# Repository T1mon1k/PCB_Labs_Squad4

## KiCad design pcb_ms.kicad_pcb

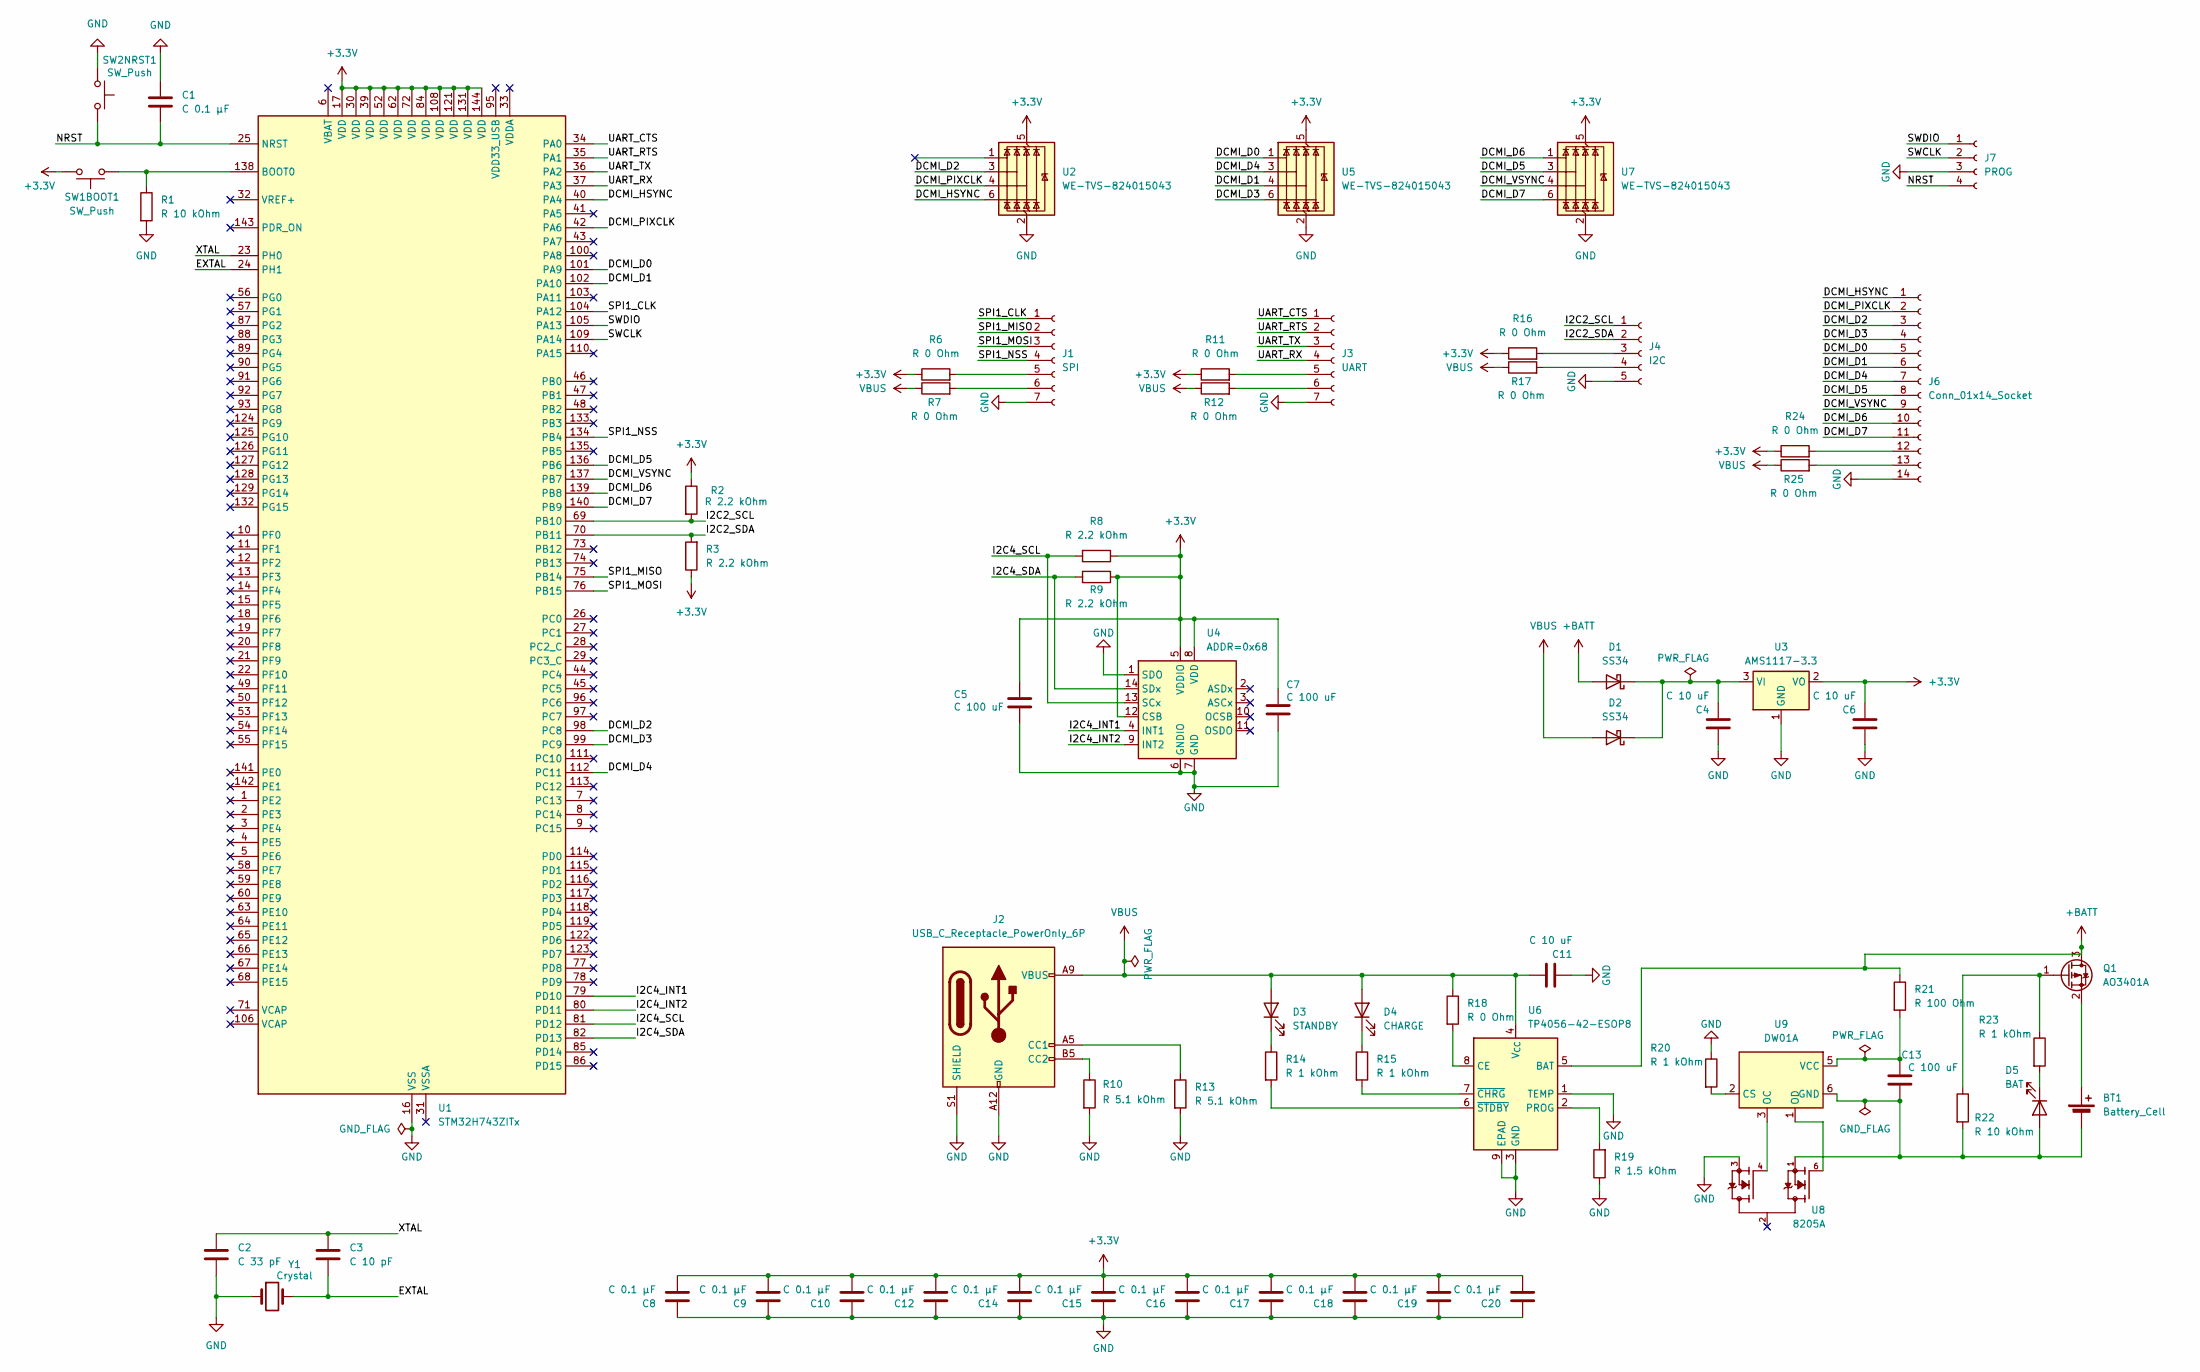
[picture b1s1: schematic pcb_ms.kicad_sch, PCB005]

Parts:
BT1: Battery_Cell; BatteryHolder_Keystone_1042_1x18650
C1, C8, C9, C10, C12, C14, C15, C16, C17, C18, C19, C20: C 0.1 μF; C_0805_2012Metric_Pad1.18x1.45mm_HandSolder
C2: C 33 pF; C_0805_2012Metric_Pad1.18x1.45mm_HandSolder
C3: C 10 pF; C_0805_2012Metric_Pad1.18x1.45mm_HandSolder
C4, C6, C11: C 10 uF; C_0805_2012Metric_Pad1.18x1.45mm_HandSolder
C5, C7, C13: C 100 uF; C_0805_2012Metric_Pad1.18x1.45mm_HandSolder
D1, D2: SS34; D_SMA
D3: STANDBY; LED_0805_2012Metric
D4: CHARGE; LED_0805_2012Metric
D5: BAT; LED_0805_2012Metric
J1: SPI; JST_ZH_S7B-ZR-SM4A-TF_1x07-1MP_P1.50mm_Horizontal
J2: USB_C_Receptacle_PowerOnly_6P; USB_C_Receptacle_GCT_USB4125-xx-x-0190_6P_TopMnt_Horizontal
J3: UART; JST_ZH_S7B-ZR-SM4A-TF_1x07-1MP_P1.50mm_Horizontal
J4: I2C; JST_ZH_S5B-ZR-SM4A-TF_1x05-1MP_P1.50mm_Horizontal
J6: Conn_01x14_Socket; JST_SH_SM14B-SRSS-TB_1x14-1MP_P1.00mm_Horizontal
J7: PROG; JST_ZH_S4B-ZR-SM4A-TF_1x04-1MP_P1.50mm_Horizontal
Q1: AO3401A; SOT-23
R1, R22: R 10 kOhm; R_0805_2012Metric_Pad1.20x1.40mm_HandSolder
R2, R3, R8, R9: R 2.2 kOhm; R_0805_2012Metric_Pad1.20x1.40mm_HandSolder
R6, R7, R11, R12, R16, R17, R18, R24, R25: R 0 Ohm; R_0805_2012Metric_Pad1.20x1.40mm_HandSolder
R10, R13: R 5.1 kOhm; R_0805_2012Metric_Pad1.20x1.40mm_HandSolder
R14, R15, R20, R23: R 1 kOhm; R_0805_2012Metric_Pad1.20x1.40mm_HandSolder
R19: R 1.5 kOhm; R_0805_2012Metric_Pad1.20x1.40mm_HandSolder
R21: R 100 Ohm; R_0805_2012Metric_Pad1.20x1.40mm_HandSolder
SW1BOOT1, SW2NRST1: SW_Push; SW_PUSH_6mm
U1: STM32H743ZITx; LQFP-144_20x20mm_P0.5mm
U2, U5, U7: WE-TVS-824015043; SOT-23-6
U3: AMS1117-3.3; SOT-223-3_TabPin2
U4: ADDR=0x68; Bosch_LGA-14_3x2.5mm_P0.5mm
U6: TP4056-42-ESOP8; SOIC-8-1EP_3.9x4.9mm_P1.27mm_EP2.41x3.3mm_ThermalVias
U8: 8205A; SOT95P285X140-6N; PARTREV NA
U9: DW01A; SOT-23-6
Y1: Crystal; Crystal_SMD_5032-2Pin_5.0x3.2mm_HandSoldering

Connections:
+3.3V: C5.2, C6.2, C7.2, C8.2, C9.2, C10.2, C12.2, C14.2, C15.2, C16.2, C17.2, C18.2, C19.2, C20.2, R2.1, R3.1, R6.1, R8.1, R9.1, R11.1, R16.1, R24.1, SW1BOOT1.2, U1.17 (VDD), U1.30 (VDD), U1.39 (VDD), U1.52 (VDD), U1.62 (VDD), U1.72 (VDD), U1.84 (VDD), U1.108 (VDD), U1.121 (VDD), U1.131 (VDD), U1.144 (VDD), U2.5 (VBUS), U3.2 (VO), U4.5 (VDDIO), U4.8 (VDD), U4.12 (CSB), U5.5 (VBUS), U7.5 (VBUS)
+BATT: D1.2 (A), Q1.3 (D), R21.1, U6.5 (BAT)
/DCMI_D0: J6.5, U1.101 (PA9), U5.1 (I/O1)
/DCMI_D1: J6.6, U1.102 (PA10), U5.4 (I/O3)
/DCMI_D2: J6.3, U1.98 (PC8), U2.3 (I/O2)
/DCMI_D3: J6.4, U1.99 (PC9), U5.6 (I/O4)
/DCMI_D4: J6.7, U1.112 (PC11), U5.3 (I/O2)
/DCMI_D5: J6.8, U1.136 (PB6), U7.3 (I/O2)
/DCMI_D6: J6.10, U1.139 (PB8), U7.1 (I/O1)
/DCMI_D7: J6.11, U1.140 (PB9), U7.6 (I/O4)
/DCMI_HSYNC: J6.1, U1.40 (PA4), U2.6 (I/O4)
/DCMI_PIXCLK: J6.2, U1.42 (PA6), U2.4 (I/O3)
/DCMI_VSYNC: J6.9, U1.137 (PB7), U7.4 (I/O3)
/EXTAL: C3.2, U1.24 (PH1), Y1.2
/I2C2_SCL: J4.1, R2.2, U1.69 (PB10)
/I2C2_SDA: J4.2, R3.2, U1.70 (PB11)
/I2C4_INT1: U1.79 (PD10), U4.4 (INT1)
/I2C4_INT2: U1.80 (PD11), U4.9 (INT2)
/I2C4_SCL: R8.2, U1.81 (PD12), U4.13 (SCx)
/I2C4_SDA: R9.2, U1.82 (PD13), U4.14 (SDx)
/NRST: C1.2, J7.4, SW2NRST1.2, U1.25 (NRST)
/SPI1_CLK: J1.1, U1.104 (PA12)
/SPI1_MISO: J1.2, U1.75 (PB14)
/SPI1_MOSI: J1.3, U1.76 (PB15)
/SPI1_NSS: J1.4, U1.134 (PB4)
/SWCLK: J7.2, U1.109 (PA14)
/SWDIO: J7.1, U1.105 (PA13)
/UART_CTS: J3.1, U1.34 (PA0)
/UART_RTS: J3.2, U1.35 (PA1)
/UART_RX: J3.4, U1.37 (PA3)
/UART_TX: J3.3, U1.36 (PA2)
/XTAL: C2.1, C3.1, U1.23 (PH0)
GND: C1.1, C2.2, C4.1, C5.1, C6.1, C7.1, C8.1, C9.1, C10.1, C11.2, C12.1, C14.1, C15.1, C16.1, C17.1, C18.1, C19.1, C20.1, J1.7, J2.A12 (GND), J2.B12 (GND), J2.S1 (SHIELD), J3.7, J4.5, J6.14, J7.3, R1.2, R10.2, R13.2, R19.1, R20.1, SW2NRST1.1, U1.16 (VSS), U1.38 (VSS), U1.51 (VSS), U1.61 (VSS), U1.83 (VSS), U1.94 (VSS), U1.107 (VSS), U1.120 (VSS), U1.130 (VSS), U2.2 (GND), U3.1 (GND), U4.1 (SDO), U4.6 (GNDIO), U4.7 (GND), U5.2 (GND), U6.1 (TEMP), U6.3 (GND), U6.9 (EPAD), U7.2 (GND), U8.3, Y1.1
unnamed: BT1.1 (+), Q1.2 (S)
unnamed: BT1.2 (-), C13.1, D5.2 (A), R22.2, U8.1, U9.6 (GND)
unnamed: C4.2, D1.1 (K), D2.1 (K), U3.3 (VI)
unnamed: D3.1 (K), R14.1
unnamed: D4.1 (K), R15.1
unnamed: D5.1 (K), R23.2
unnamed: J1.5, R6.2
unnamed: J1.6, R7.2
unnamed: J2.A5 (CC1), R13.1
unnamed: J2.B5 (CC2), R10.1
unnamed: J3.5, R11.2
unnamed: J3.6, R12.2
unnamed: J4.3, R16.2
unnamed: J4.4, R17.2
unnamed: J6.12, R24.2
unnamed: J6.13, R25.2
unnamed: Q1.1 (G), R22.1, R23.1
unnamed: R1.1, SW1BOOT1.1, U1.138 (BOOT0)
unnamed: R18.2, U6.8 (CE)
unnamed: R19.2, U6.2 (PROG)
unnamed: R15.2, U6.7 (~CHRG)
unnamed: R14.2, U6.6 (~STDBY)
unnamed: R20.2, U9.2 (CS)
unnamed: U8.4, U9.3 (OC)
unnamed: U8.6, U9.1 (OD)
unnamed: C13.2, R21.2, U9.5 (VCC)
VBUS: C11.1, D2.2 (A), D3.2 (A), D4.2 (A), J2.A9 (VBUS), J2.B9 (VBUS), R7.1, R12.1, R17.1, R18.1, R25.1, U6.4 (V_{CC})

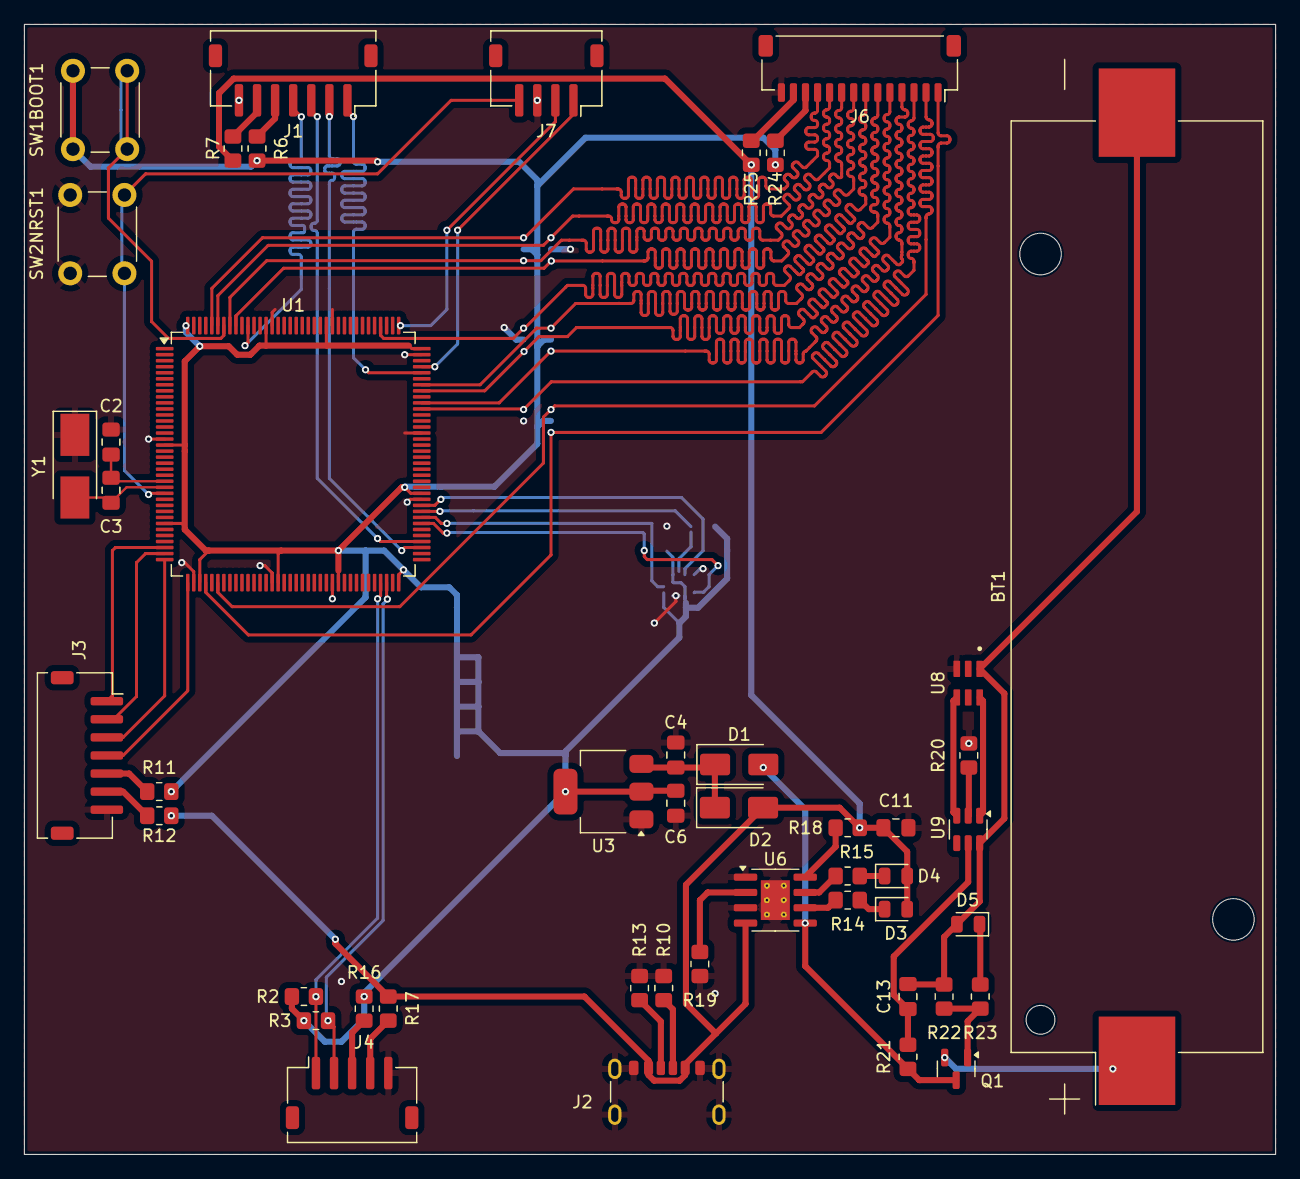
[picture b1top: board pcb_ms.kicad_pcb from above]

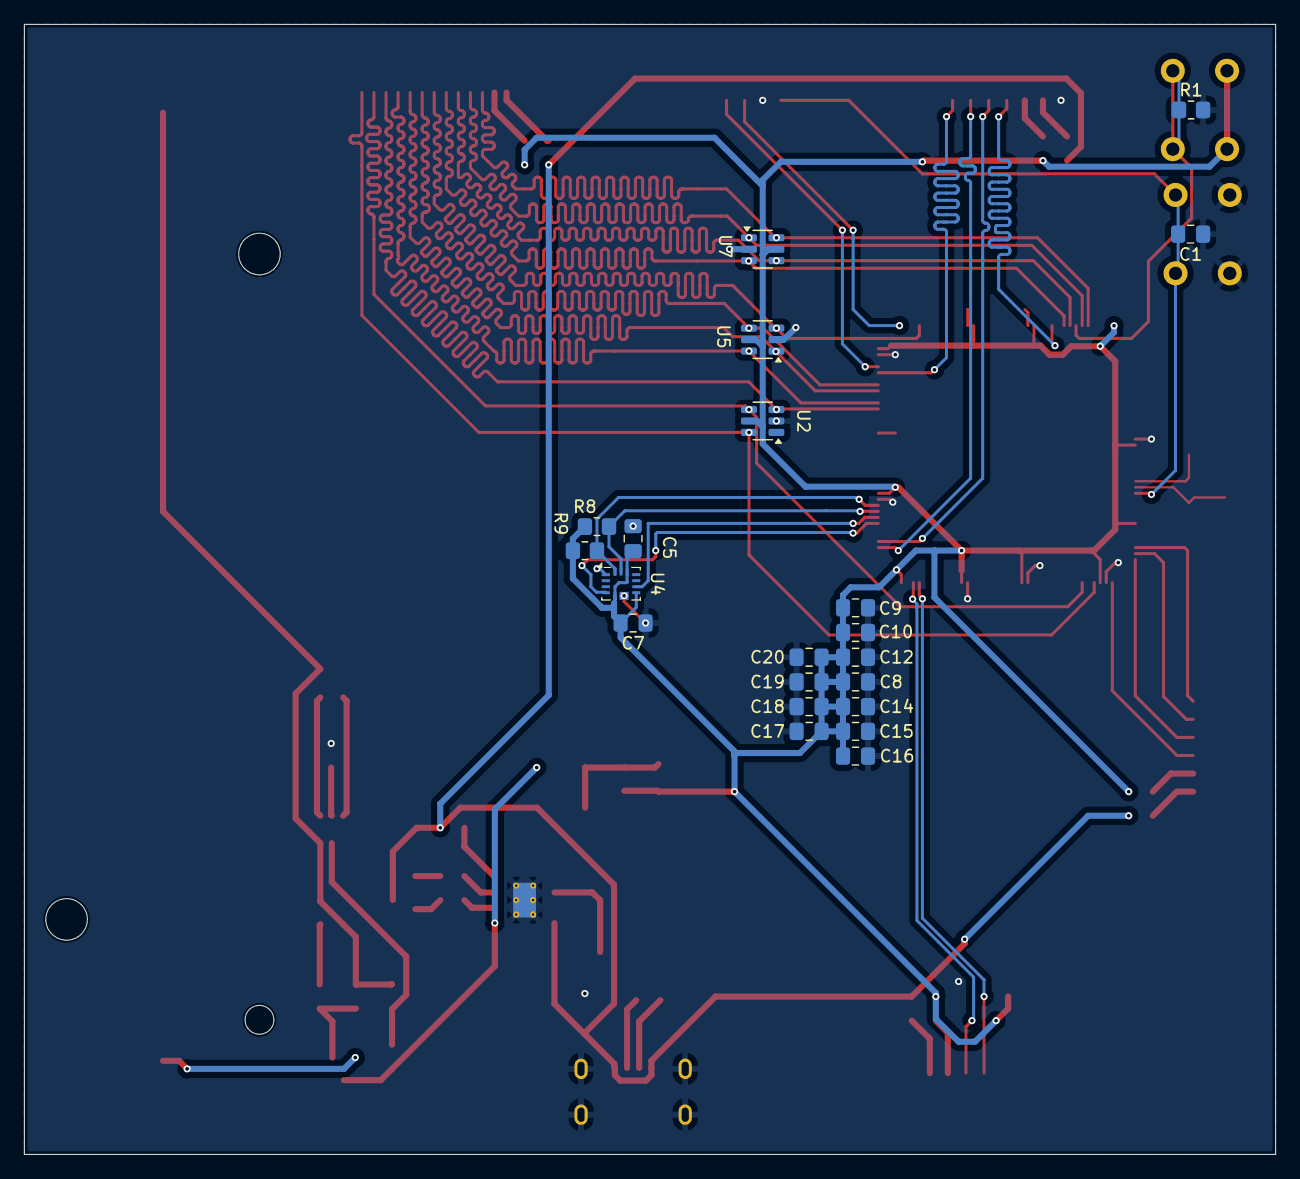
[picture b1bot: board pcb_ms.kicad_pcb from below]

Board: 2 copper layers, 103.8 x 93.8 mm, 68 parts (21 on the bottom side), 60 nets.

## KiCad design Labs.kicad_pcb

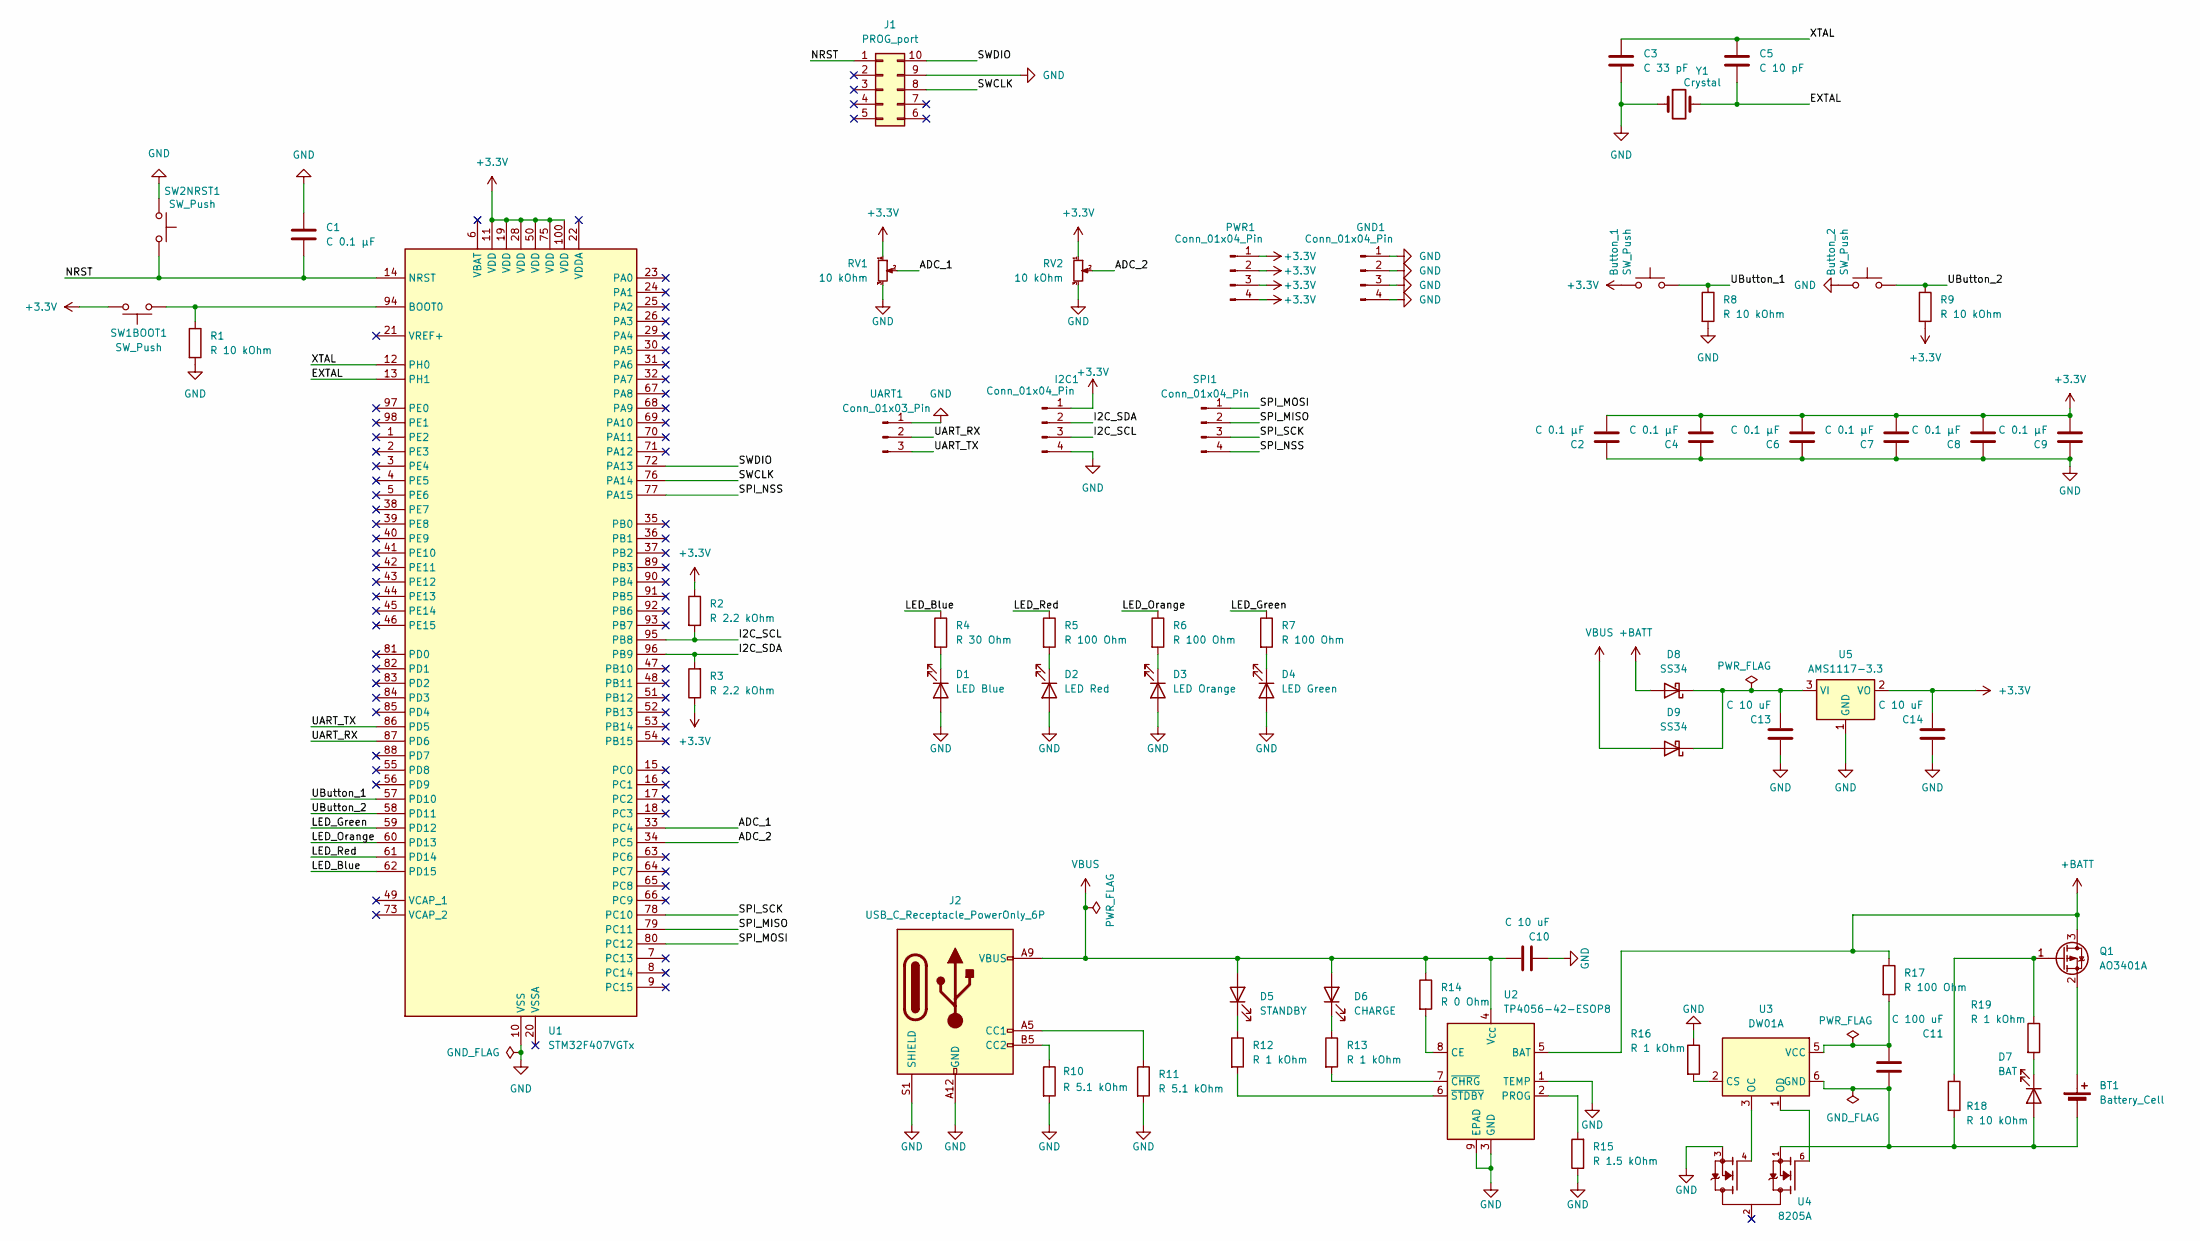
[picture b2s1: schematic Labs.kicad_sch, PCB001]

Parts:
BT1: Battery_Cell; BatteryHolder_MPD_BH-18650-PC
Button_1, Button_2: SW_Push; SW_PUSH_6mm
C1, C2, C4, C6, C7, C8, C9: C 0.1 μF; C_0805_2012Metric_Pad1.18x1.45mm_HandSolder
C3: C 33 pF; C_0805_2012Metric_Pad1.18x1.45mm_HandSolder
C5: C 10 pF; C_0805_2012Metric_Pad1.18x1.45mm_HandSolder
C10, C13, C14: C 10 uF; C_0805_2012Metric_Pad1.18x1.45mm_HandSolder
C11: C 100 uF; C_0805_2012Metric_Pad1.18x1.45mm_HandSolder
D1: LED Blue; LED_0805_2012Metric
D2: LED Red; LED_0805_2012Metric
D3: LED Orange; LED_0805_2012Metric
D4: LED Green; LED_0805_2012Metric
D5: STANDBY; LED_0805_2012Metric
D6: CHARGE; LED_0805_2012Metric
D7: BAT; LED_0805_2012Metric
D8, D9: SS34; D_SMA
GND1: Conn_01x04_Pin; PinHeader_1x04_P2.54mm_Horizontal
I2C1: Conn_01x04_Pin; PinHeader_1x04_P2.54mm_Horizontal
J1: PROG_port; PinHeader_2x05_P2.54mm_Vertical
J2: USB_C_Receptacle_PowerOnly_6P; USB_C_Receptacle_GCT_USB4125-xx-x-0190_6P_TopMnt_Horizontal
PWR1: Conn_01x04_Pin; PinHeader_1x04_P2.54mm_Horizontal
Q1: AO3401A; SOT-23
R1, R8, R9, R18: R 10 kOhm; R_0805_2012Metric_Pad1.20x1.40mm_HandSolder
R2, R3: R 2.2 kOhm; R_0805_2012Metric_Pad1.20x1.40mm_HandSolder
R4: R 30 Ohm; R_0805_2012Metric_Pad1.20x1.40mm_HandSolder
R5, R6, R7, R17: R 100 Ohm; R_0805_2012Metric_Pad1.20x1.40mm_HandSolder
R10, R11: R 5.1 kOhm; R_0805_2012Metric_Pad1.20x1.40mm_HandSolder
R12, R13, R16, R19: R 1 kOhm; R_0805_2012Metric_Pad1.20x1.40mm_HandSolder
R14: R 0 Ohm; R_0805_2012Metric_Pad1.20x1.40mm_HandSolder
R15: R 1.5 kOhm; R_0805_2012Metric_Pad1.20x1.40mm_HandSolder
RV1, RV2: 10 kOhm; Potentiometer_Bourns_3266Y_Vertical
SPI1: Conn_01x04_Pin; PinHeader_1x04_P2.54mm_Horizontal
SW1BOOT1, SW2NRST1: SW_Push; SW_PUSH_6mm
U1: STM32F407VGTx; LQFP-100_14x14mm_P0.5mm
U2: TP4056-42-ESOP8; SOIC-8-1EP_3.9x4.9mm_P1.27mm_EP2.41x3.3mm_ThermalVias
U3: DW01A; SOT-23-6
U4: 8205A; SOT95P285X140-6N; PARTREV NA
U5: AMS1117-3.3; SOT-223-3_TabPin2
UART1: Conn_01x03_Pin; PinHeader_1x03_P2.54mm_Horizontal
Y1: Crystal; Crystal_SMD_5032-2Pin_5.0x3.2mm_HandSoldering

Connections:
+3.3V: Button_1.1, C2.2, C4.2, C6.2, C7.2, C8.2, C9.2, C14.2, I2C1.1, PWR1.1, PWR1.2, PWR1.3, PWR1.4, R2.1, R3.1, R9.2, RV1.1, RV2.1, SW1BOOT1.2, U1.11 (VDD), U1.19 (VDD), U1.28 (VDD), U1.50 (VDD), U1.75 (VDD), U1.100 (VDD), U5.2 (VO)
+BATT: D8.2 (A), Q1.3 (D), R17.1, U2.5 (BAT)
/ADC_1: RV1.2, U1.33 (PC4)
/ADC_2: RV2.2, U1.34 (PC5)
/EXTAL: C5.2, U1.13 (PH1), Y1.2
/I2C_SCL: I2C1.3, R2.2, U1.95 (PB8)
/I2C_SDA: I2C1.2, R3.2, U1.96 (PB9)
/LED_Blue: R4.1, U1.62 (PD15)
/LED_Green: R7.1, U1.59 (PD12)
/LED_Orange: R6.1, U1.60 (PD13)
/LED_Red: R5.1, U1.61 (PD14)
/NRST: C1.2, J1.1, SW2NRST1.2, U1.14 (NRST)
/SPI_MISO: SPI1.2, U1.79 (PC11)
/SPI_MOSI: SPI1.1, U1.80 (PC12)
/SPI_NSS: SPI1.4, U1.77 (PA15)
/SPI_SCK: SPI1.3, U1.78 (PC10)
/SWCLK: J1.8, U1.76 (PA14)
/SWDIO: J1.10, U1.72 (PA13)
/UART_RX: U1.87 (PD6), UART1.2
/UART_TX: U1.86 (PD5), UART1.3
/UButton_1: Button_1.2, R8.1, U1.57 (PD10)
/UButton_2: Button_2.2, R9.1, U1.58 (PD11)
/XTAL: C3.1, C5.1, U1.12 (PH0)
GND: Button_2.1, C1.1, C2.1, C3.2, C4.1, C6.1, C7.1, C8.1, C9.1, C10.2, C13.1, C14.1, D1.2 (A), D2.2 (A), D3.2 (A), D4.2 (A), GND1.1, GND1.2, GND1.3, GND1.4, I2C1.4, J1.9, J2.A12 (GND), J2.B12 (GND), J2.S1 (SHIELD), R1.2, R8.2, R10.2, R11.2, R15.1, R16.1, RV1.3, RV2.3, SW2NRST1.1, U1.10 (VSS), U1.27 (VSS), U1.74 (VSS), U1.99 (VSS), U2.1 (TEMP), U2.3 (GND), U2.9 (EPAD), U4.3, U5.1 (GND), UART1.1, Y1.1
unnamed: BT1.1 (+), Q1.2 (S)
unnamed: BT1.2 (-), C11.1, D7.2 (A), R18.2, U3.6 (GND), U4.1
unnamed: D1.1 (K), R4.2
unnamed: D2.1 (K), R5.2
unnamed: D3.1 (K), R6.2
unnamed: D4.1 (K), R7.2
unnamed: D5.1 (K), R12.1
unnamed: D6.1 (K), R13.1
unnamed: D7.1 (K), R19.2
unnamed: C13.2, D8.1 (K), D9.1 (K), U5.3 (VI)
unnamed: J2.A5 (CC1), R11.1
unnamed: J2.B5 (CC2), R10.1
unnamed: Q1.1 (G), R18.1, R19.1
unnamed: R1.1, SW1BOOT1.1, U1.94 (BOOT0)
unnamed: R14.2, U2.8 (CE)
unnamed: R15.2, U2.2 (PROG)
unnamed: R13.2, U2.7 (~CHRG)
unnamed: R12.2, U2.6 (~STDBY)
unnamed: R16.2, U3.2 (CS)
unnamed: U3.3 (OC), U4.4
unnamed: U3.1 (OD), U4.6
unnamed: C11.2, R17.2, U3.5 (VCC)
VBUS: C10.1, D5.2 (A), D6.2 (A), D9.2 (A), J2.A9 (VBUS), J2.B9 (VBUS), R14.1, U2.4 (V_{CC})

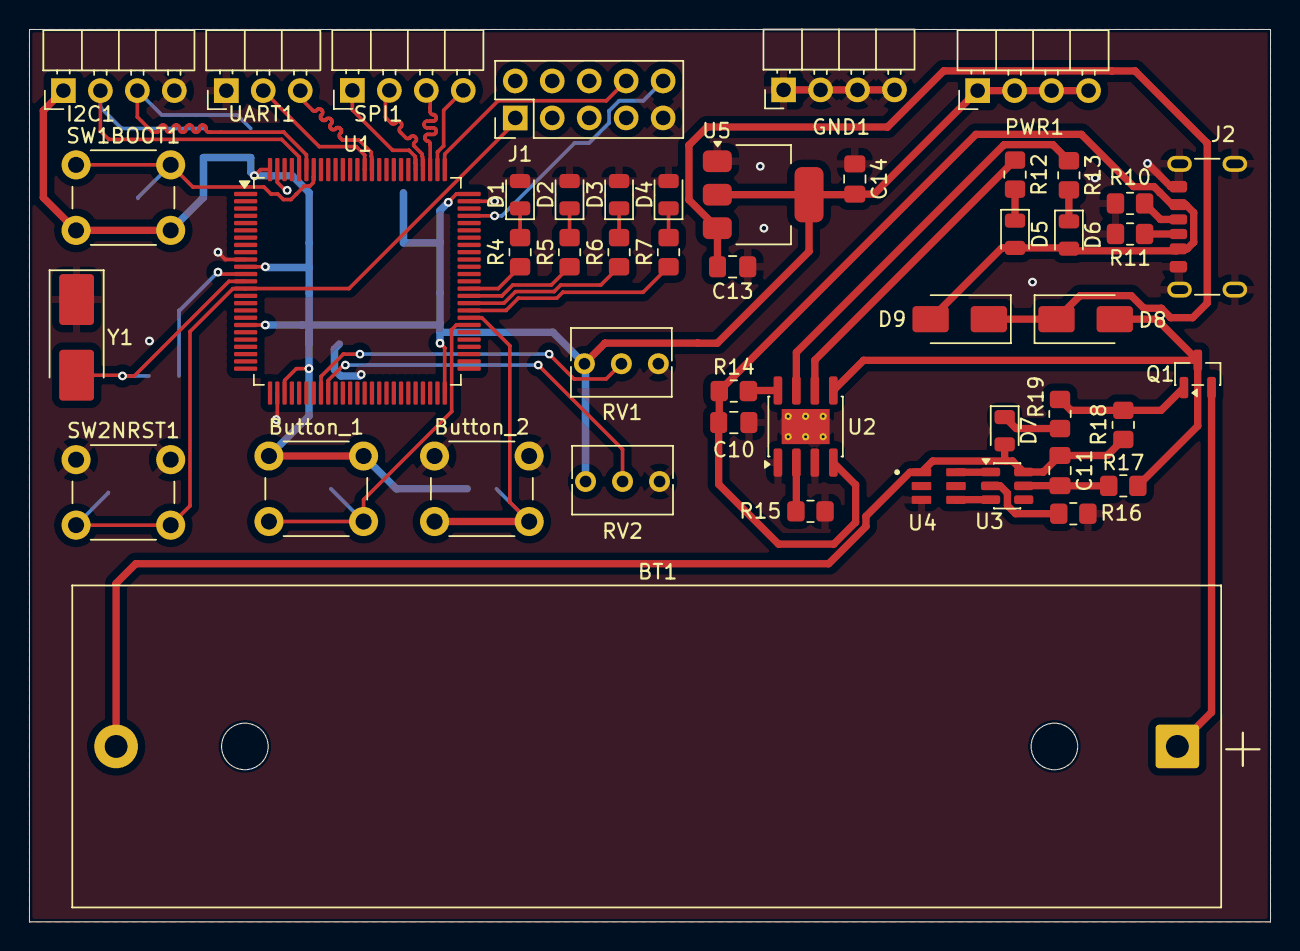
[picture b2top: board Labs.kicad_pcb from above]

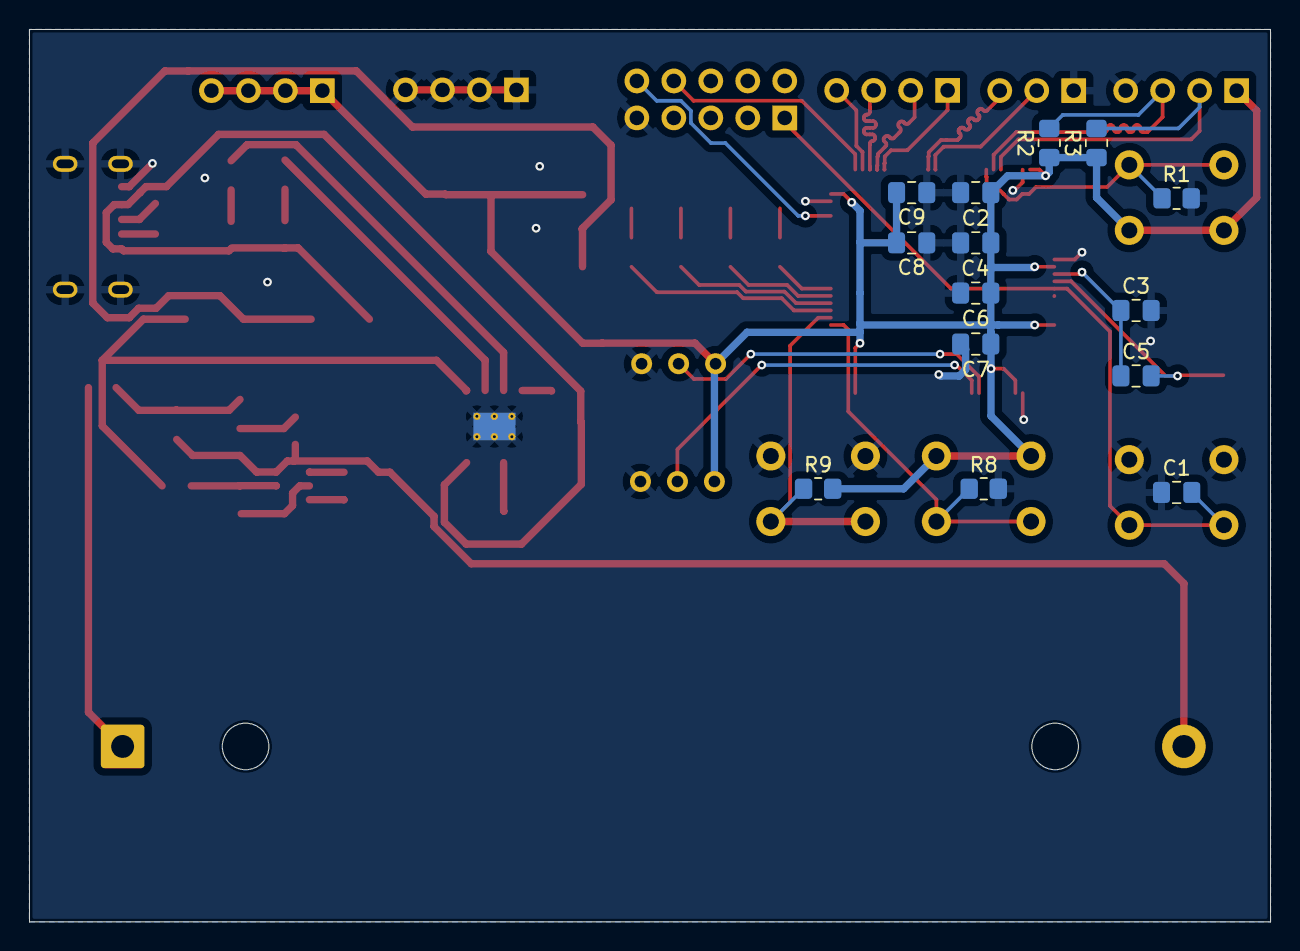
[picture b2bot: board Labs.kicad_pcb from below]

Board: 2 copper layers, 85.2 x 61.3 mm, 62 parts (14 on the bottom side), 47 nets.

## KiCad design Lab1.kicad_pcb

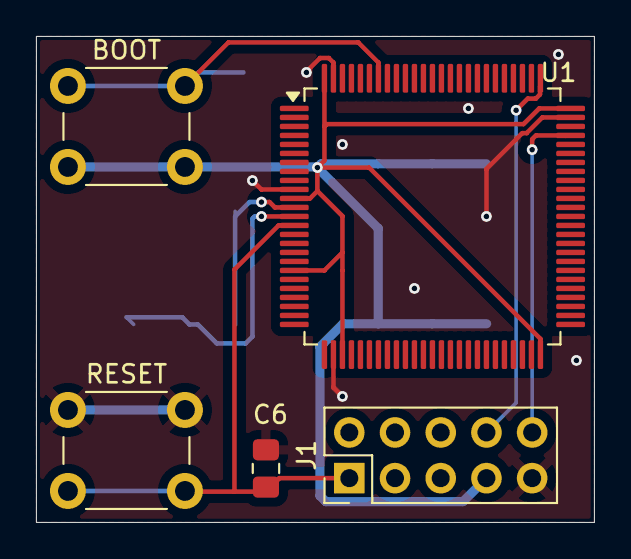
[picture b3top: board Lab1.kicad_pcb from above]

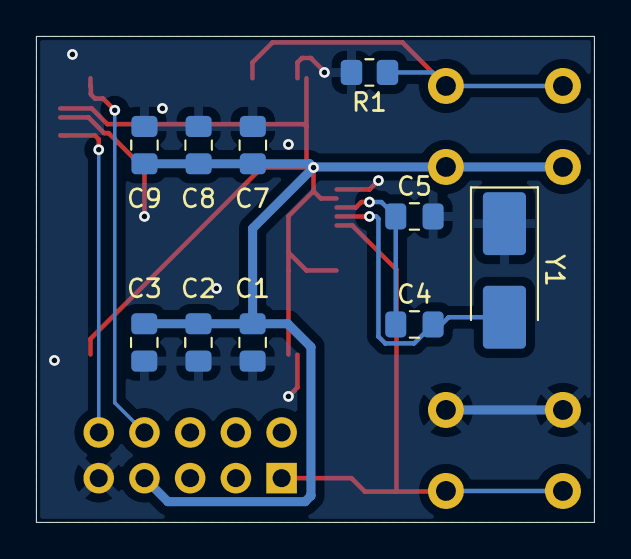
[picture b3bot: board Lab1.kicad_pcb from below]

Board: 2 copper layers, 31.0 x 27.0 mm, 15 parts (10 on the bottom side), 8 nets.

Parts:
BOOT: SW_Push; SW_PUSH_6mm
C1, C2, C3, C6, C7, C8, C9: C 0.1 μF; C_0805_2012Metric_Pad1.18x1.45mm_HandSolder
C4: C 10 pF; C_0805_2012Metric_Pad1.18x1.45mm_HandSolder
C5: C 33 pF; C_0805_2012Metric_Pad1.18x1.45mm_HandSolder
J1: Conn_02x05_Counter_Clockwise; PinHeader_2x05_P2.54mm_Vertical
R1: R 10 kOhm; R_0805_2012Metric_Pad1.20x1.40mm_HandSolder
RESET: SW_Push; SW_PUSH_6mm
U1: STM32F407VGTx; LQFP-100_14x14mm_P0.5mm
Y1: Crystal; Crystal_SMD_5032-2Pin_5.0x3.2mm_HandSoldering

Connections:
+3.3V: BOOT.2, C1.2, C2.2, C3.2, C7.2, C8.2, C9.2, J1.7, U1.11 (VDD), U1.19 (VDD), U1.28 (VDD), U1.50 (VDD), U1.75 (VDD), U1.100 (VDD)
/EXTAL: C4.2, U1.13 (PH1), Y1.2
/NRST: C6.2, J1.1, RESET.2, U1.14 (NRST)
/SWCLK: J1.8, U1.76 (PA14)
/SWDIO: J1.10, U1.72 (PA13)
/XTAL: C4.1, C5.1, U1.12 (PH0)
GND: C1.1, C2.1, C3.1, C5.2, C6.1, C7.1, C8.1, C9.1, J1.9, R1.2, RESET.1, U1.10 (VSS), U1.27 (VSS), U1.74 (VSS), U1.99 (VSS), Y1.1
unnamed: BOOT.1, R1.1, U1.94 (BOOT0)

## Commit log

2026-03-12 feat: Add schematic
2026-03-12 feat: Update footprints for buttons and add Libs
2026-03-14 fix: add ERC power input
    feat: structure the diagram into modules
    refactor: change global labels to local
    feat: add PCB board
    feat: make ERC adnd DRC check
2026-03-14 chore: add stamp
2026-03-15 fix: change side J1
2026-03-15 feat: simple schema draw
2026-03-15 fix: clean backups
2026-03-15 fix: simple schema draw
2026-04-04 feat: add GPIO pins
    feat: add user buttons
    feat: add user LED
    feat: add user potentiometer
2026-04-04 feat: add tracing
2026-04-05 feat: add structure schematic
2026-04-05 chore: rename files
2026-04-05 feat: add communication interfaces
2026-04-08 fix: minor fixes
2026-04-08 fix: silkscreen
2026-04-25 feat: add pwr supply from type-c connector
    feat: add pwr supply from bat
    feat: add dc/dc lower pwr
    feat: add pwr for extern sensors
    fix: replace adc to another pin
2026-04-27 feat: add simple schema
2026-04-27 chore: remove generated kicad files
2026-05-15 feat: add STM32 multisensor KiCad PCB project
